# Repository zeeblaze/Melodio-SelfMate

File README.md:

Melodio Self-Mate is a cutting-edge portable electronic device designed to revolutionize your music experience. At its core lies the powerful ESP32-S3, providing unparalleled performance and versatility. This innovative gadget seamlessly combines music playback, Spotify streaming, and programmability, making it the go-to choice for music enthusiasts and programmers that wants to look into how smart devices work.

This portable programmable device packs a lot into its little brain, including and not Limited to, IR(receiver and transmitter), High speed mass storage, SD card, touch wheel technology, USB switch, which gives it a endless possibility of what is achievable with it. 

# KEY FEATURES:

ESP32-S3: Melodio makes use of ESP32-S3 as its heart which ensures high-performance and efficiency, enabling a seamless user experience.

DAC: Melodio uses the high quality TI PCM5102A 32bit, 348kHz, 112dB audio stereo DAC to output digital audio signal coming from the ESP32-S3 as analog signal for the headphone amplifier.

HEADPHONE AMP: High quality analog audio signal coming from the PCM5102A is received by yet another high quality headphone amplifier from Texas Instrument, TI TPA6130A2 138-mW stereo analog input headphone amplifier with I2C control interface, which then output its amplified audio signal to a headphone jack. The I2c control interface of this amplifier allows the volume of the amplifier output audio to be controlled from the software.

DISPLAY: Melodio implements a 1.8 inch 128x160 ST7735 TFT display as a visual interface.

MASS STORAGE

USB SWITCH

BUTTONS: There are four buttons on the side of Melodio:

Volume Up
Volume Down
Boot_0(for entering programming mode)
Reset
Volume Up and Volume Down buttons control the  headphone amp directly from software, so their functionalities can be altered and hardcode the amplifier volume directly from software. 

SLIDER SWITCHES

SPOTIFY CONNECT

MUSIC PLAYER

STEMMA QT CONNECTOR

IR (Transmitter and Receiver)

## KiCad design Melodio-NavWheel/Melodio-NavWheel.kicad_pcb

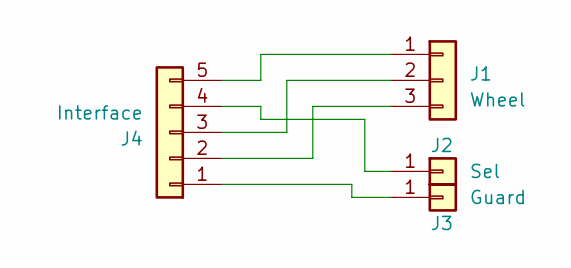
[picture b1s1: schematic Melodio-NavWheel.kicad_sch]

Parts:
J1: Wheel; qtouch-wheel
J2: Sel; qtouch-button
J3: Guard; qtouch-guard
J4: Interface; PinHeader_1x05_P1.27mm_Vertical

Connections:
unnamed: J1.1, J4.5
unnamed: J1.2, J4.3
unnamed: J1.3, J4.2
unnamed: J2.1, J4.4
unnamed: J3.1, J4.1

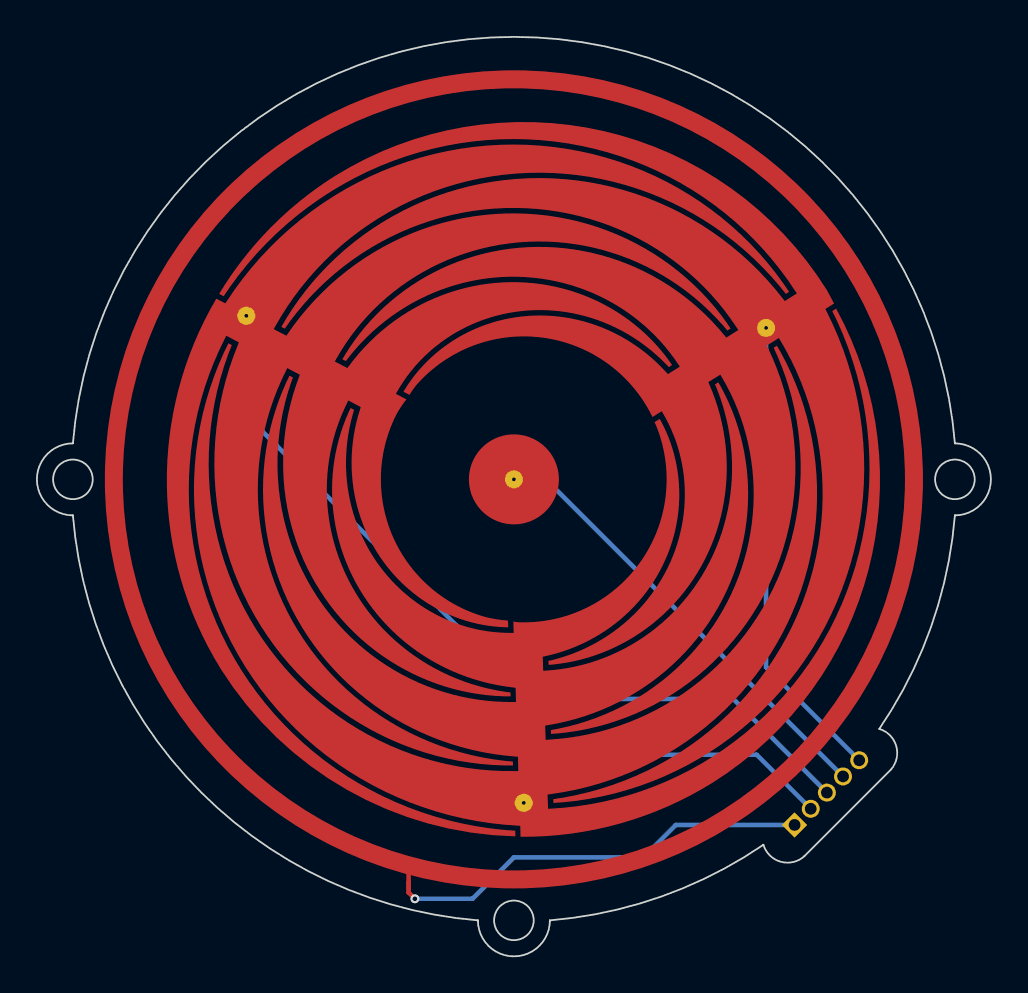
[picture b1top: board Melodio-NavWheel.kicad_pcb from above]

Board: 2 copper layers, 53.0 x 51.1 mm, 4 parts (1 on the bottom side), 5 nets.

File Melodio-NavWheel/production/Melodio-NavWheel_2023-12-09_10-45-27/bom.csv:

Designator,Footprint,Quantity,Value,LCSC Part #
J1,qtouch-wheel,1,Wheel,
J2,qtouch-button,1,Sel,
J3,qtouch-guard,1,Guard,
J4,PinHeader_1x05_P1.27mm_Vertical,1,Interface,

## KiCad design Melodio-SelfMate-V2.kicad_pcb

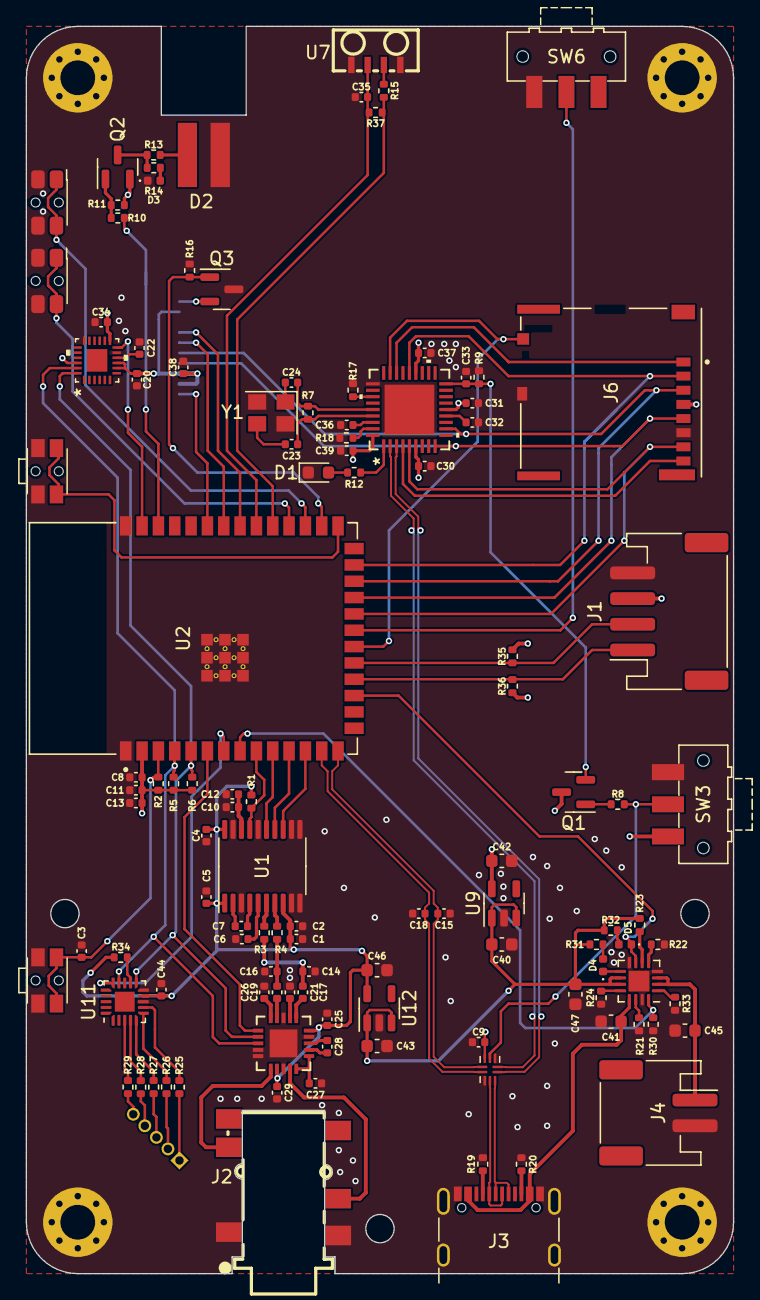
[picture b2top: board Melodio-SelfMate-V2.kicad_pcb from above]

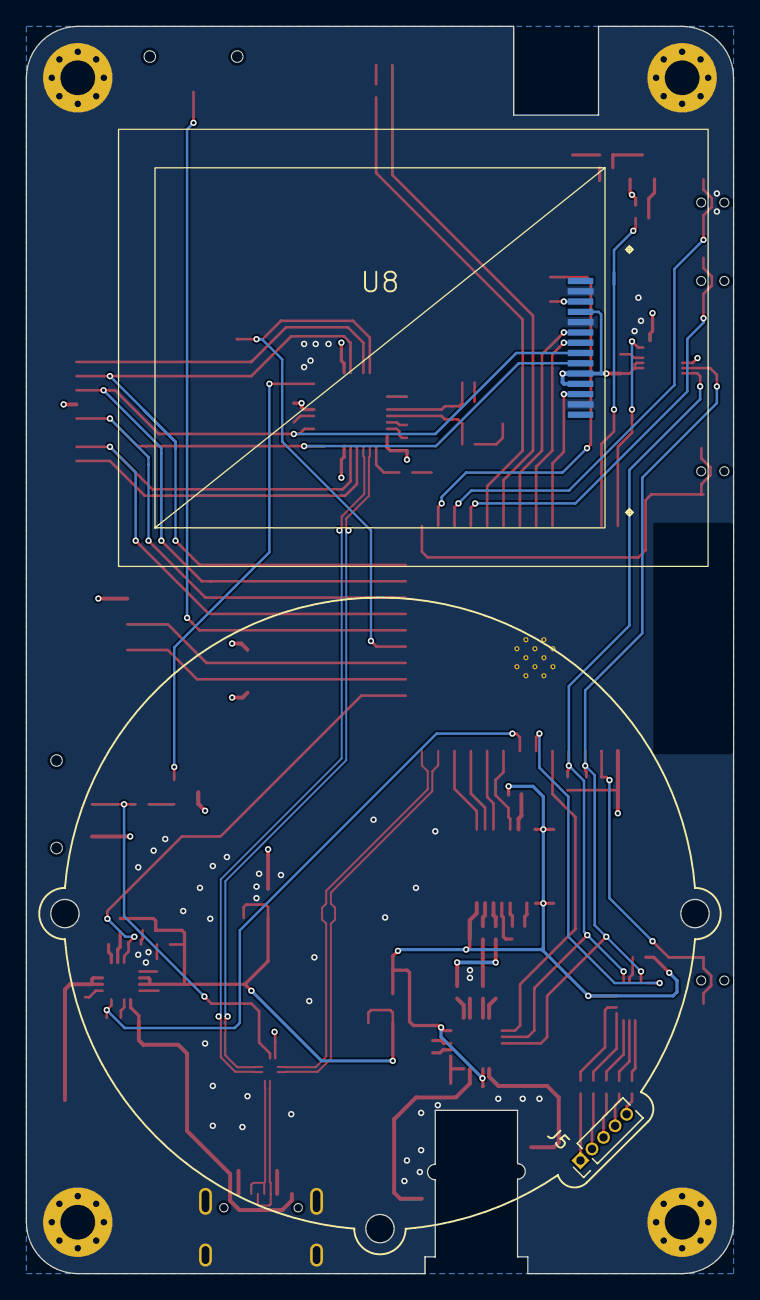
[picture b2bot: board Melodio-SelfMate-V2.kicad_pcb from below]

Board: 4 copper layers, 55.0 x 97.0 mm, 121 parts (2 on the bottom side), 102 nets.

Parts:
C1, C11, C13: 10u; C_0402_1005Metric
C2, C4, C5, C8, C9, C10, C20, C22, C35: 100n; C_0402_1005Metric
C3, C12, C17, C19, C21, C23, C24, C25, C26, C27, C28, C29, C30, C31, C32, C33, C34, C36, C37, C38, C39, C44: 1u; C_0402_1005Metric
C6, C7: 2u2; C_0402_1005Metric
C14, C16: 2n2; C_0402_1005Metric
C15, C18: DNP; C_0402_1005Metric
C40, C41, C42, C43, C45, C46, C47: 10u; C_0603_1608Metric
D1: GREEN; LED_0603_1608Metric
D2: SFH4346; LED_5mm_Side_Mount
D3, D4: RED; LED_0402_1005Metric
D5: GREEN; LED_0402_1005Metric
H1, H2, H3, H4: MountingHole_Pad; MountingHole_2.7mm_M2.5_Pad_Via
J1: STEMMA_QT; JST_PH_S4B-PH-SM4-TB_1x04-1MP_P2.00mm_Horizontal
J2: SMD_PJ-399E-6A
J3: USB_C_Receptacle_USB2.0; USB_C_Receptacle_GCT_USB4105-xx-A_16P_TopMnt_Horizontal
J4: BATTERY_CONN; JST_PH_S2B-PH-SM4-TB_1x02-1MP_P2.00mm_Horizontal
J5: Qtouch; PinHeader_1x05_P1.27mm_Vertical
J6: Micro_SD_Card_Det2; MOLEX_503398-1892
Q1, Q2, Q3: DMG2301L; SOT-23
R1, R2, R8, R11, R14, R17, R18, R21, R22, R23, R25, R26, R27, R28, R29, R33, R34, R37: 10k; R_0402_1005Metric
R3, R4: 470R; R_0402_1005Metric
R5, R6, R35, R36: 4k7; R_0402_1005Metric
R7, R16: 1mR; R_0402_1005Metric
R9, R12, R15, R31, R32: 1k; R_0402_1005Metric
R10: 330R; R_0402_1005Metric
R13: 200R; R_0402_1005Metric
R19, R20: 5k1; R_0402_1005Metric
R24, R30: 1k1; R_0402_1005Metric
SW1: BOOT; SW_SPST_EVQP7C
SW2: RST; SW_SPST_EVQP7C
SW3, SW6: SW_USB; SW_SPDT_CK-JS102011SAQN
SW4: VOL_UP; SW_SPST_EVQP7C
SW5: VOL_DOWN; SW_SPST_EVQP7C
U1: PCM5102; TSSOP-20_4.4x6.5mm_P0.65mm
U2: ESP32-S3-WROOM-1-N4R4; ESP32-S3-WROOM-1-N8R8
U3: USB3740B-AI2; UQFN-10_1.3x1.8mm_P0.4mm
U4: MPU-6500
U5: TPA6130A2RTJR
U6: USB2244-AEZG-06
U7: IRM-V838M3-C-TR1
U8: 1.8inch_TFT_128x160
U9, U12: AP2112K-3.3; SOT-23-5
U10: BQ24075RGT; VQFN-16-1EP_3x3mm_P0.5mm_EP1.6x1.6mm
U11: VQFN-20-1EP_3x3mm_P0.45mm_EP1.55x1.55mm
Y1: 24MHz; Crystal_SMD_3225-4Pin_3.2x2.5mm

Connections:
+3.3VA: C1.2, C2.2, C4.2, C5.2, C25.1, C29.1, C44.2, C46.1, R1.2, R34.2, U1.1 (CPVDD), U1.8 (AVDD), U1.20 (DVDD), U5.12 (VDD_2), U5.20 (VDD), U11.9 (VDD), U12.5 (VOUT)
+3V3: C8.1, C9.2, C11.1, C13.1, C20.1, C30.2, C31.2, C34.1, C37.2, C38.1, C39.2, C42.1, J1.3, J6.4 (VDD), Q1.3 (D), Q2.2 (S), R2.1, R5.2, R6.2, R11.1, R35.2, R36.2, SW3.1 (A), U2.2 (3V3), U3.5 (VDD), U4.8 (VDDIO), U4.9 (SDO/ADO), U4.13 (VDD), U4.22 (nCS), U6.6 (VDD33), U6.14 (VDD33), U6.22 (VDD33), U6.36 (VDDA33), U8.4 (LEDA), U8.10 (VCC), U8.11 (VCC2), U9.5 (VOUT)
+5V: C40.1, C43.1, C47.1, R23.2, R31.1, R32.1, U9.1 (VIN), U9.3 (EN), U10.10 (OUT), U10.11 (OUT), U12.1 (VIN), U12.3 (EN)
+BATT: C45.1, J4.1, U10.2 (BAT), U10.3 (BAT)
/CHG: D5.1 (K), U2.17 (IO9), U10.7 (~PGOOD)
/DISP_CS: U2.35 (IO42), U8.12 (CS)
/DISP_EN: Q3.1 (G), R16.2, U2.28 (IO35)
/DISP_RS: U2.34 (IO41), U8.7 (RS/DC)
/DISP_RST: U2.33 (IO40), U8.6 (RESET)
/EN1: R23.1, U10.6 (EN1)
/EN2: R22.2, U10.5 (EN2)
/HP_OUTL: J2.3, U5.14 (HPLEFT)
/HP_OUTR: J2.4, U5.11 (HPRIGHT)
/I2C1_SCL: J1.1, R36.1, U2.18 (IO10)
/I2C1_SDA: J1.2, R35.1, U2.19 (IO11)
/IMU_INT: U2.39 (IO1), U4.12 (INT)
/IO0: SW1.1, U2.27 (IO0)
/IR_LED: R10.1, U2.38 (IO2)
/IR_RX: R15.1, R37.1, U2.31 (IO38)
/IR_VCC: C35.2, R37.2, U2.32 (IO39), U7.2 (VCC)
/LOCK: SW6.2 (B), U2.21 (IO13)
/L_OUT: R3.1, U1.6 (OUTL)
/R_OUT: R4.1, U1.7 (OUTR)
/SD_CLK: J6.5 (CLK), U2.23 (IO21), U6.9 (SD_CLK), U8.9 (CLOCK)
/SD_CMD: J6.3 (CMD), U2.24 (IO47), U6.11 (SD_CMD), U8.8 (DATA)
/SD_CS: J6.2 (DAT3/CD), U2.25 (IO48), U6.23 (SD_D3)
/SD_DAT0: J6.7 (DAT0), U2.22 (IO14), U6.5 (SD_D0)
/SD_DAT1: J6.8 (DAT1), U6.4 (SD_D1)
/SD_DAT2: J6.1 (DAT2), U6.25 (SD_D2)
/SD_DET: J6.9 (DET), U2.20 (IO12), U6.26 (SD_NCD)
/TOUCH_INT: U2.7 (IO7), U11.15 (~CHANGE)
/USB1_D+: U3.2 (DP_1), U6.2 (USB+)
/USB1_D-: U3.1 (DM_1), U6.3 (USB-)
/USB2_D+: C15.1, U2.14 (IO20), U3.6 (DP_2)
/USB2_D-: C18.1, U2.13 (IO19), U3.7 (DM_2)
/USB_SW: R8.2, SW3.2 (B), U3.4 (S)
/VBUS: C41.1, J3.A4 (VBUS), J3.A9 (VBUS), J3.B4 (VBUS), J3.B9 (VBUS), U10.13 (IN)
/VOL_DOWN: SW5.1, U2.30 (IO37)
/VOL_UP: SW4.1, U2.29 (IO36)
/XIN: C23.2, R7.2, U6.33 (XTAL1(CLKIN))
/XTAL2: C24.2, R7.1, U6.32 (XTAL2)
AMP_SD: U2.6 (IO6), U5.6 (~SD)
CHG_ADC: R30.2, U2.8 (IO15), U10.16 (ISET)
DIN: U1.14 (DIN), U2.11 (IO18)
GND: C1.1, C2.1, C3.2, C4.1, C5.1, C6.1, C8.2, C9.1, C10.1, C11.2, C12.1, C13.2, C14.1, C15.2, C16.1, C18.2, C20.2, C21.2, C22.1, C25.2, C26.2, C27.1, C29.2, C30.1, C31.1, C32.2, C33.1, C34.2, C35.1, C36.1, C37.1, C38.2, C39.1, C40.2, C41.2, C42.2, C43.2, C44.1, C45.2, C46.2, C47.2, D1.1 (K), D2.1 (K), D3.1 (K), H1.1, H2.1, H3.1, H4.1, J1.4, J2.1, J2.2, J3.A1 (GND), J3.A12 (GND), J3.B1 (GND), J3.B12 (GND), J3.S1 (SHIELD), J4.2, J6.6 (VSS), J6.10 (SHIELD), Q3.3 (D), R9.1, R16.1, R17.1, R18.2, R19.2, R20.1, R21.1, R22.1, R24.1, R30.1, R33.2, SW1.2, SW2.2, SW3.3 (C), SW4.2, SW5.2, SW6.3 (C), U1.3 (CPGND), U1.9 (AGND), U1.10 (DEMP), U1.11 (FLT), U1.12 (SCK), U1.16 (FMT), U1.19 (DGND), U2.1 (GND), U2.40 (GND__1), U2.41_1 (GND__2), U2.41_2 (GND__3), U2.41_3 (GND__4), U2.41_4 (GND__5), U2.41_5 (GND__6), U2.41_6 (GND__7), U2.41_7 (GND__8), U2.41_8 (GND__9), U2.41_9 (GND__10), U3.3 (OE_N), U3.8 (GND), U4.11 (FSYNC), U4.18 (GND), U5.3 (GND_2), U5.9 (GND_3), U5.10 (GND_4), U5.13 (GND_5), U5.19 (GND), U5.21 (EP), U6.28 (TEST), U6.37 (EPAD), U7.1 (GND), U7.4 (GND), U8.2 (GND), U8.5 (GND1), U8.13 (GND2), U9.2 (GND), U10.4 (~CE), U10.8 (VSS), U10.15 (SYSOFF), U10.17 (VSS), U11.8 (VSS), U11.10 (MODE), U12.2 (GND), Y1.2, Y1.4
I2C_SCL: R5.1, U2.4 (IO4), U4.23 (SCL/SCLK), U5.8 (SCL), U11.14 (SCL)
I2C_SDA: R6.1, U2.5 (IO5), U4.24 (SDA/SDI), U5.7 (SDA), U11.11 (SDA)
I2S_BCLK: U1.13 (BCK), U2.12 (IO8)
I2S_LRCLK: U1.15 (LRCK), U2.10 (IO17)
MUTE: R1.1, U1.17 (XSMT), U2.9 (IO16)
unnamed: C14.2, C17.2, R3.2
unnamed: C16.2, C19.2, R4.2
unnamed: C23.1, Y1.3
unnamed: C24.1, Y1.1
unnamed: D1.2 (A), R12.2
unnamed: D2.2 (A), R13.2
unnamed: D3.2 (A), R14.2
unnamed: D4.2 (A), R31.2
unnamed: D4.1 (K), U10.9 (~CHG)
unnamed: D5.2 (A), R32.2
unnamed: J3.A5 (CC1), R19.1
unnamed: J3.B5 (CC2), R20.2
unnamed: J5.1, R25.1
unnamed: J5.2, R26.1
unnamed: J5.3, R27.1
unnamed: J5.4, R28.1
unnamed: J5.5, R29.1
unnamed: Q1.1 (G), R8.1
unnamed: C33.2, Q1.2 (S), R9.2, U6.18 (RESET_N)
unnamed: Q2.3 (D), R13.1, R14.1
unnamed: Q2.1 (G), R10.2, R11.2
unnamed: Q3.2 (S), U8.3 (LEDK)
unnamed: C7.1, U1.4 (CAPM)
unnamed: C7.2, U1.2 (CAPP)
unnamed: C10.2, C12.2, U1.18 (LDOO)
unnamed: C6.2, U1.5 (VNEG)
unnamed: C3.1, R2.2, SW2.1, U2.3 (EN)
unnamed: C22.2, U4.10 (REGOUT)
unnamed: C28.2, U5.17 (CPN)
unnamed: C28.1, U5.18 (CPP)
unnamed: C27.2, U5.15 (CPVSS_2), U5.16 (CPVSS)
unnamed: C17.1, U5.1 (LEFTINM)
unnamed: C21.1, U5.2 (LEFTINP)
unnamed: C26.1, U5.5 (RIGHTINM)
unnamed: C19.1, U5.4 (RIGHTINP)
unnamed: R12.1, U6.1 (LED)
unnamed: R18.1, U6.35 (RBIAS)
unnamed: R17.2, U6.30 (SD_WP)
unnamed: C32.1, U6.13 (VDD18)
unnamed: C36.2, U6.34 (VDD18PLL)
unnamed: R15.2, U7.3 (OUT)
unnamed: R24.2, U10.12 (ILIM)
unnamed: R21.2, U10.14 (TMR)
unnamed: R33.1, U10.1 (TS)
unnamed: R25.2, U11.7 (KEY0)
unnamed: R26.2, U11.6 (KEY1)
unnamed: R27.2, U11.5 (KEY2)
unnamed: R28.2, U11.4 (KEY3)
unnamed: R29.2, U11.3 (KEY4)
unnamed: R34.1, U11.12 (~RESET)
USB_D+: J3.A6 (D+), J3.B6 (D+), U3.10 (DP)
USB_D-: J3.A7 (D-), J3.B7 (D-), U3.9 (DM)

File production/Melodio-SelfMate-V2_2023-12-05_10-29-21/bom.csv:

Designator,Footprint,Quantity,Value,LCSC Part #
"C1, C11, C13",0402,3,10u,
"C10, C2, C20, C22, C35, C4, C5, C8, C9",0402,9,100n,
"C12, C17, C19, C21, C23, C24, C25, C26, C27, C28, C29, C3, C30, C31, C32, C33, C34, C36, C37, C38, C39, C44",0402,22,1u,
"C14, C16",0402,2,2n2,
"C15, C18",0402,2,DNP,
"C40, C41, C42, C43, C45, C46, C47",0603,7,10u,
"C6, C7",0402,2,2u2,
D1,0603,1,GREEN,
D2,LED_5mm_Side_Mount,1,SFH4346,
"D3, D4",0402,2,RED,
D5,0402,1,GREEN,
"H1, H2, H3, H4",MountingHole_2.7mm_M2.5_Pad_Via,4,MountingHole_Pad,
J1,JST_PH_S4B-PH-SM4-TB_1x04-1MP_P2.00mm_Horizontal,1,STEMMA_QT,
J2,SMD_PJ-399E-6A,1,~,
J3,USB_C_Receptacle_GCT_USB4105-xx-A_16P_TopMnt_Horizontal,1,USB_C_Receptacle_USB2.0,
J4,JST_PH_S2B-PH-SM4-TB_1x02-1MP_P2.00mm_Horizontal,1,BATTERY_CONN,
J5,PinHeader_1x05_P1.27mm_Vertical,1,Qtouch,
J6,MOLEX_503398-1892,1,Micro_SD_Card_Det2,
"Q1, Q2, Q3",SOT-23,3,DMG2301L,
"R1, R11, R14, R17, R18, R2, R21, R22, R23, R25, R26, R27, R28, R29, R33, R34, R37, R8",0402,18,10k,
R10,0402,1,330R,
"R12, R15, R31, R32, R9",0402,5,1k,
R13,0402,1,200R,
"R16, R7",0402,2,1mR,
"R19, R20",0402,2,5k1,
"R24, R30",0402,2,1k1,
"R3, R4",0402,2,470R,
"R35, R36, R5, R6",0402,4,4k7,
SW1,SW_SPST_EVQP7C,1,BOOT,
SW2,SW_SPST_EVQP7C,1,RST,
"SW3, SW6",SW_SPDT_CK-JS102011SAQN,2,SW_USB,
SW4,SW_SPST_EVQP7C,1,VOL_UP,
SW5,SW_SPST_EVQP7C,1,VOL_DOWN,
U1,TSSOP-20_4.4x6.5mm_P0.65mm,1,PCM5102,
U10,VQFN-16-1EP_3x3mm_P0.5mm_EP1.6x1.6mm,1,BQ24075RGT,
U11,VQFN-20-1EP_3x3mm_P0.45mm_EP1.55x1.55mm,1,~,
"U12, U9",SOT-23-5,2,AP2112K-3.3,
U2,ESP32-S3-WROOM-1-N8R8,1,ESP32-S3-WROOM-1-N4R4,
U3,UQFN-10_1.3x1.8mm_P0.4mm,1,USB3740B-AI2,
U4,MPU-6500,1,MPU-6500,
U5,TPA6130A2RTJR,1,TPA6130A2RTJR,TPA6130A2RTJR
U6,USB2244-AEZG-06,1,USB2244-AEZG-06,
U7,IRM-V838M3-C-TR1,1,~,
U8,1.8inch_TFT_128x160,1,~,
Y1,Crystal_SMD_3225-4Pin_3.2x2.5mm,1,24MHz,

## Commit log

2023-12-09 project files
2023-12-09 readme file
2023-12-09 readme file_update

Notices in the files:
parts and their libraries:
Copyright 2021 Accelerated Designs. All rights reserved.
